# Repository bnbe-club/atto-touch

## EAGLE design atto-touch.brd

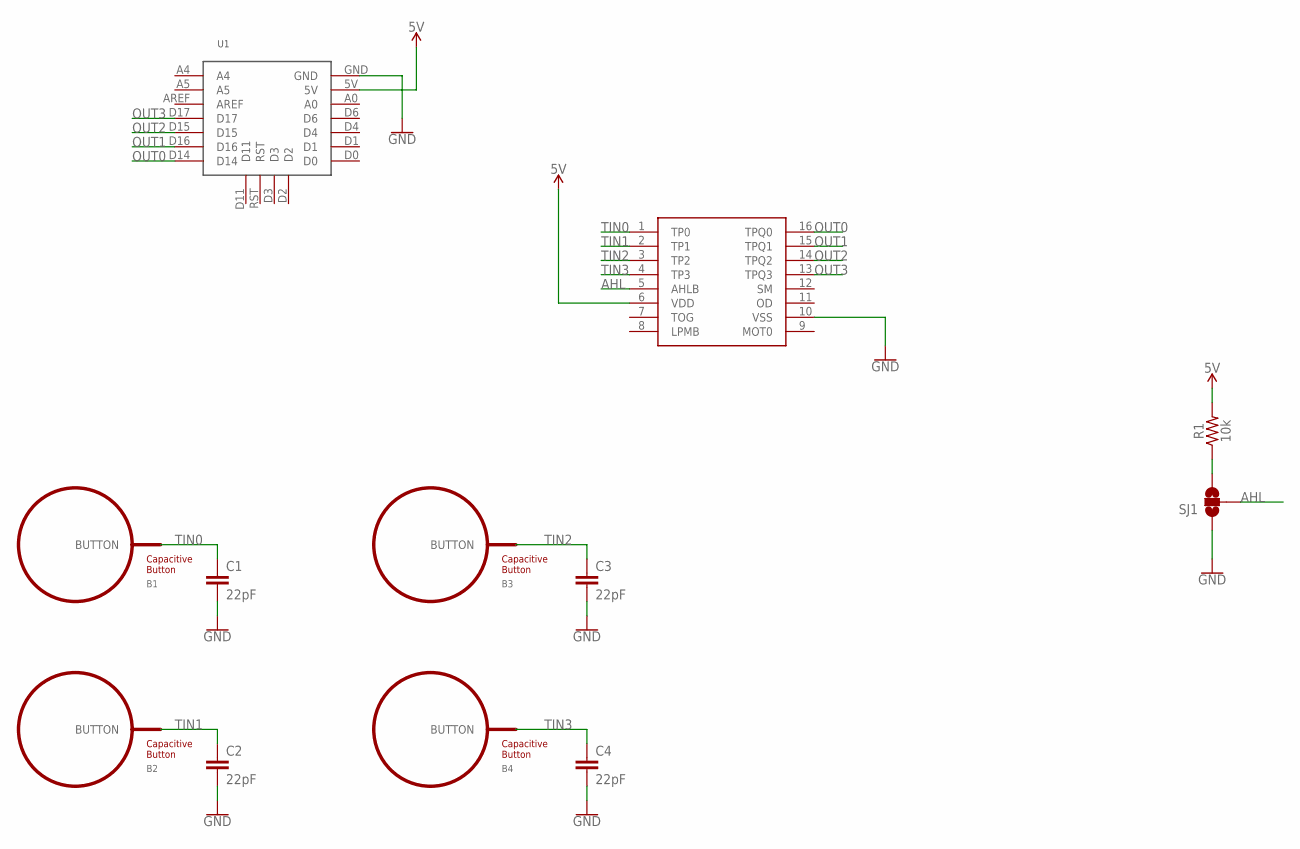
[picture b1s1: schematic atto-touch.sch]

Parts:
B1, B2, B3, B4: BUTTON_PASSIVE10MM; BUTTON_PASSIVE_10MM
C1, C2, C3, C4: 22pF; 0603
R1: 10k; 0603
SJ1: SOLDERJUMPER_2WAYS; SJ_3
U1: PIKSEY_ATTO
U2: TTP224; SSOP-16

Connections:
5V: R1.2, U1.5V, U2.6 (VDD)
AHL: SJ1.2, U2.5 (AHLB)
GND: C1.2, C2.2, C3.2, C4.2, SJ1.1, U1.GND, U2.10 (VSS)
unnamed: R1.1, SJ1.3
OUT0: U1.D14, U2.16 (TPQ0)
OUT1: U1.D16, U2.15 (TPQ1)
OUT2: U1.D15, U2.14 (TPQ2)
OUT3: U1.D17, U2.13 (TPQ3)
TIN0: B1.BUTTON, C1.1, U2.1 (TP0)
TIN1: B2.BUTTON, C2.1, U2.2 (TP1)
TIN2: B3.BUTTON, C3.1, U2.3 (TP2)
TIN3: B4.BUTTON, C4.1, U2.4 (TP3)

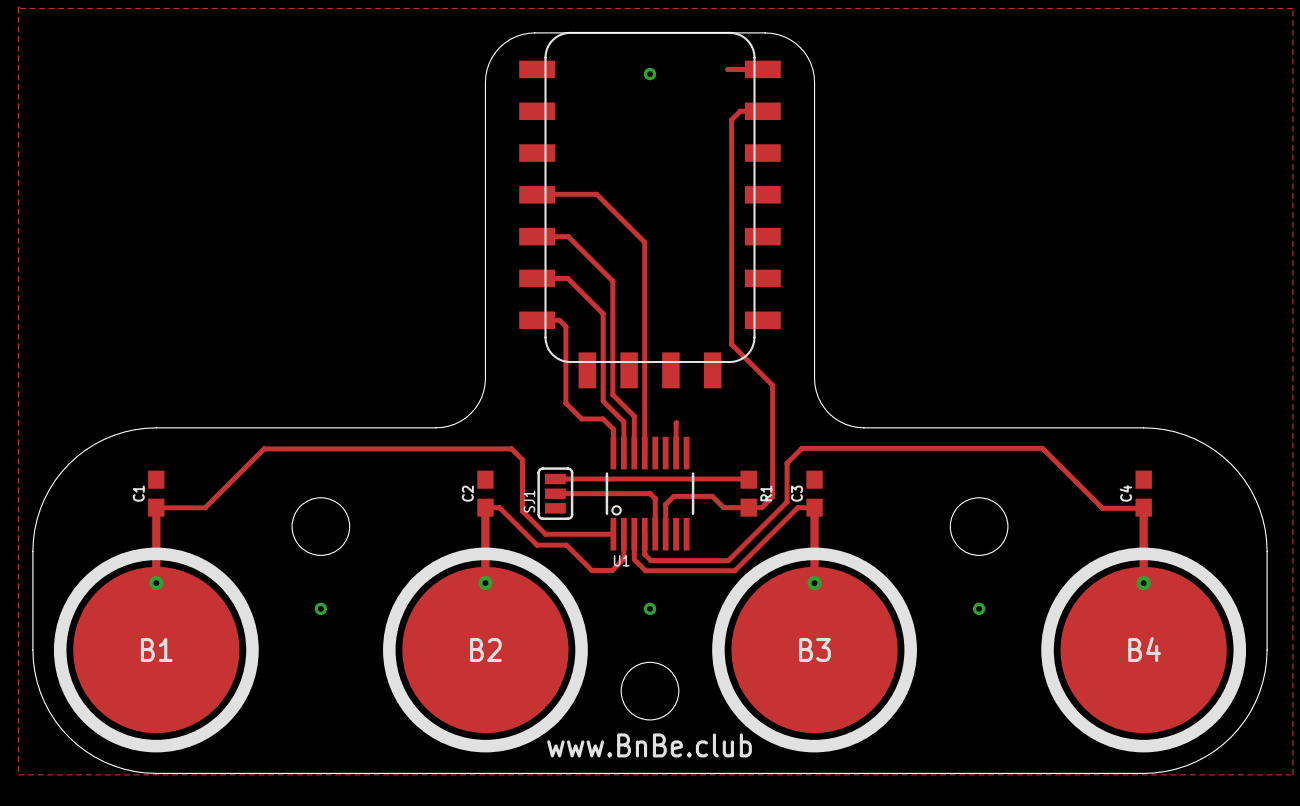
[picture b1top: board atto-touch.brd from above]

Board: 2 copper layers, 75.0 x 45.0 mm, 12 parts (0 on the bottom side), 12 nets.

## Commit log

2020-01-10 Initial release

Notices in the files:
parts and their libraries:
PatternAgents-TouchWidgets: License : http://creativecommons.org/licenses/by-sa/4.0/ (Creative Commons 4.0)
PatternAgents-TouchWidgets: License : http://creativecommons.org/licenses/by-sa/3.1/ (Creative Commons 3.1)
